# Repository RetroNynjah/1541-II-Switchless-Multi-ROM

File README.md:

# Retroninja 1541-II Switchless Multi-ROM
<br/>
A microcontroller based switchless ROM switcher for the Commodore 1541-II disk drive.
Switch between stock CBM DOS, JiffyDOS and other ROMs by issuing commands from Basic.
No computer modifications or drive enclosure modifications needed. Completely reversible drive modification.

Read the user's guide for more information.

# A new revision of this board has been released under the more generic name [Switchless Multi-ROM for 27128 & 27256](https://github.com/RetroNynjah/Switchless-Multi-ROM-for-27128-27256)

  <br/>

## BOM
 |Component|Pcs |Name|Comment|
 |:--------|---:|:---|:------|
 | SST39SF010A | 1 | IC1 | Flash. SST39SF020/040 should work too. PLCC-32 |
 | ATMEGA328P-AU | 1 | IC2 | Or compatible ATmega8/48/88/168/328 variants. TQFP-32 |
 | 74AHCT273NSR | 1 | IC4 | Flip-Flop SO-20 (5.3mm width) |
 | 74AHCT1G04 | 1 | IC5 | Inverter single gate SOT-23 |
 | 100nF ceramic capacitor | 4 | C1, C2, C3, C4 | 0805 |
 | 30pF ceramic capacitor | 2 | C5, C6 | 0805 - 22pF works too |
 | 10k resistor | 1 | R1 | 0805 |
 | 560R resistor | 1 | R2 | 0805 - LED current limiting resistor|
 | LED | 1 | D1 | 1206 |
 | ECS-160-20-3X-TR | 1 | XTAL1 | Crystal 16MHz |
 | 14 pin header | 2 | "IC3" | Male machined pin headers or flat headers. 2.54mm pitch. To fit DIL-28 socket. |
 | 6 pin header right-angled | 1 | JP1 | Optional 2.54mm pitch. For ISP programmer. |

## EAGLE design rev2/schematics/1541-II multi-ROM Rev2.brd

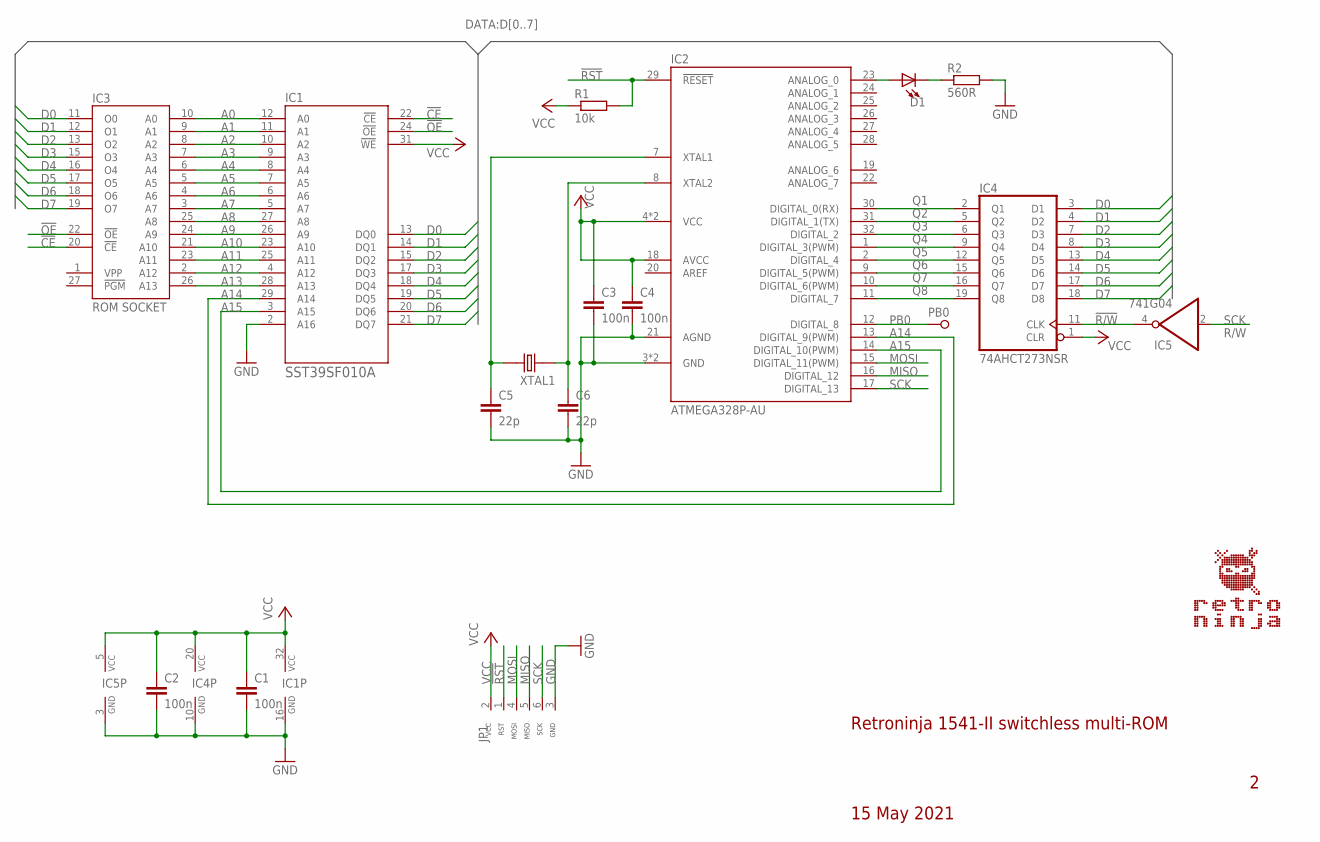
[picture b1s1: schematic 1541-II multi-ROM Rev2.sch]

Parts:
C1, C2, C3, C4: 100n; C0805
C5, C6: 22p; C0805
D1: LED_1206; LED1206
IC1: SST39SF010A; PLCC32_SHORT
IC2: ATMEGA328P-AU; TQFP32
IC3: ROM SOCKET; DIL28-6_DOWNPINS
IC4: 74AHCT273NSR; SO20
IC5: 741G04; SOT23-5
JP1: ICSP_CONNECTOR_TL866_RIGHT2; HEADER_1X6_RIGHT
PB0: TEST_POINT_TH
R1: 10k; R0805
R2: 560R; R0805
XTAL1: CRYSTAL; CRYSTAL_SMD-2_7X4X2.3

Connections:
!CE: IC1.22 (!CE), IC3.20 (!CE)
!OE: IC1.24 (!OE), IC3.22 (!OE)
!R/W: IC4.11 (CLK), IC5.4 (O)
!RST: IC2.29 (!RESET), JP1.1 (RST), R1.2
A0: IC1.12 (A0), IC3.10 (A0)
A1: IC1.11 (A1), IC3.9 (A1)
A2: IC1.10 (A2), IC3.8 (A2)
A3: IC1.9 (A3), IC3.7 (A3)
A4: IC1.8 (A4), IC3.6 (A4)
A5: IC1.7 (A5), IC3.5 (A5)
A6: IC1.6 (A6), IC3.4 (A6)
A7: IC1.5 (A7), IC3.3 (A7)
A8: IC1.27 (A8), IC3.25 (A8)
A9: IC1.26 (A9), IC3.24 (A9)
A10: IC1.23 (A10), IC3.21 (A10)
A11: IC1.25 (A11), IC3.23 (A11)
A12: IC1.4 (A12), IC3.2 (A12)
A13: IC1.28 (A13), IC3.26 (A13)
A14: IC1.29 (A14), IC2.13 (DIGITAL_9(PWM))
A15: IC1.3 (A15), IC2.14 (DIGITAL_10(PWM))
D0: IC1.13 (DQ0), IC3.11 (O0), IC4.3 (D1)
D1: IC1.14 (DQ1), IC3.12 (O1), IC4.4 (D2)
D2: IC1.15 (DQ2), IC3.13 (O2), IC4.7 (D3)
D3: IC1.17 (DQ3), IC3.15 (O3), IC4.8 (D4)
D4: IC1.18 (DQ4), IC3.16 (O4), IC4.13 (D5)
D5: IC1.19 (DQ5), IC3.17 (O5), IC4.14 (D6)
D6: IC1.20 (DQ6), IC3.18 (O6), IC4.17 (D7)
D7: IC1.21 (DQ7), IC3.19 (O7), IC4.18 (D8)
GND: C1.2, C2.2, C3.2, C4.2, C5.2, C6.2, IC1.2 (A16), IC1.16 (GND), IC2.3 (GND), IC2.5 (GND), IC2.21 (AGND), IC3.14 (GND), IC4.10 (GND), IC5.3 (GND), JP1.3 (GND), R2.2
MISO: IC2.16 (DIGITAL_12), JP1.5 (MISO)
MOSI: IC2.15 (DIGITAL_11(PWM)), JP1.4 (MOSI)
unnamed: C6.1, IC2.8 (XTAL2), XTAL1.1
unnamed: C5.1, IC2.7 (XTAL1), XTAL1.2
unnamed: D1.A, IC2.23 (ANALOG_0)
unnamed: D1.C, R2.1
PB0: IC2.12 (DIGITAL_8), PB0.P$1
Q1: IC2.30 (DIGITAL_0(RX)), IC4.2 (Q1)
Q2: IC2.31 (DIGITAL_1(TX)), IC4.5 (Q2)
Q3: IC2.32 (DIGITAL_2), IC4.6 (Q3)
Q4: IC2.1 (DIGITAL_3(PWM)), IC4.9 (Q4)
Q5: IC2.2 (DIGITAL_4), IC4.12 (Q5)
Q6: IC2.9 (DIGITAL_5(PWM)), IC4.15 (Q6)
Q7: IC2.10 (DIGITAL_6(PWM)), IC4.16 (Q7)
Q8: IC2.11 (DIGITAL_7), IC4.19 (Q8)
SCK: IC2.17 (DIGITAL_13), IC5.2 (I), JP1.6 (SCK)
VCC: C1.1, C2.1, C3.1, C4.1, IC1.31 (!WE), IC1.32 (VCC), IC2.4 (VCC), IC2.6 (VCC), IC2.18 (AVCC), IC3.28 (VCC), IC4.1 (CLR), IC4.20 (VCC), IC5.5 (VCC), JP1.2 (VCC), R1.1

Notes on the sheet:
R/W
Retroninja 1541-II switchless multi-ROM
15 May 2021

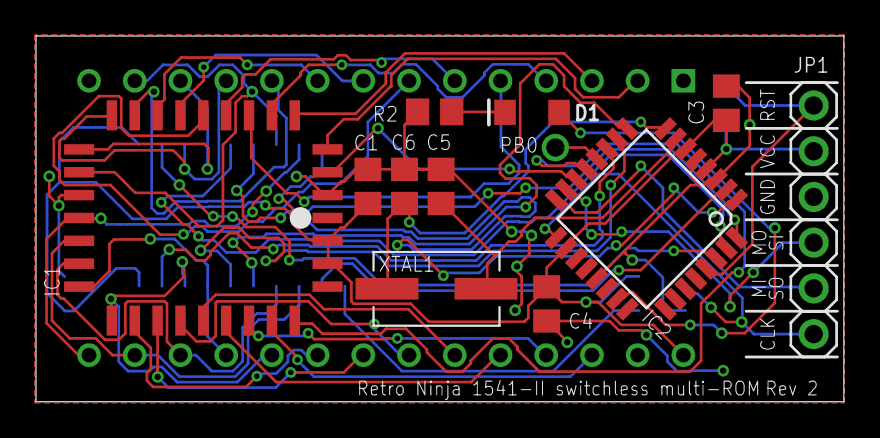
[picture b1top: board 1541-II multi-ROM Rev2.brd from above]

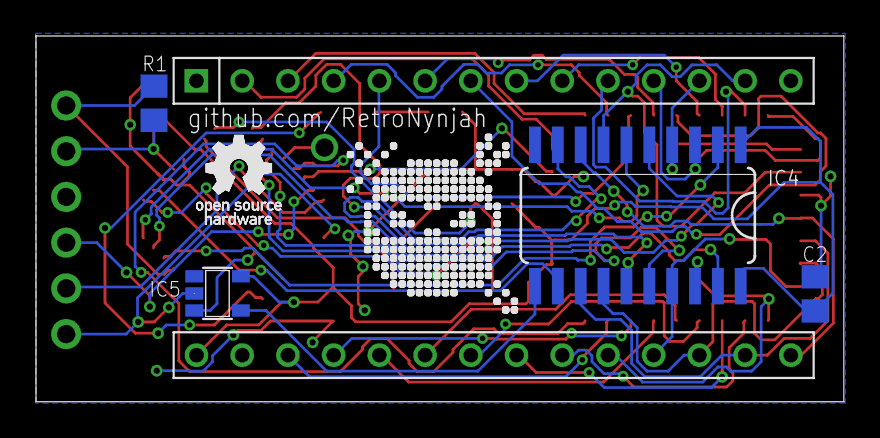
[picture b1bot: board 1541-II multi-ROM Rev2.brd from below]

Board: 2 copper layers, 44.9 x 20.3 mm, 19 parts (6 on the bottom side), 46 nets.

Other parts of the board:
U$1: RETRONINJA_NOTEXT_10MM
U$2: OSHW_5MM

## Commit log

2021-05-15 Update README.md
    Adjusted BOM
2021-05-15 Updated images
2021-05-15 Update README.md
    Updated images
2021-05-15 Update README.md
    Corrected SMD LED size
2021-05-22 Updated README and User's Guide
    Updated information about parts, MCU's and programming. User's Guide change history section added.
2022-07-05 Replaced 1541-II_RomSwitcher_Sketch.ino
    Wrong file uploaded
